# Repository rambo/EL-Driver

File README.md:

# EL driver

Trying to build as small as possible (and relatively efficiente) EL driver
for small panels/wires for wearable applications.

Currently looking at using Micrel ICs

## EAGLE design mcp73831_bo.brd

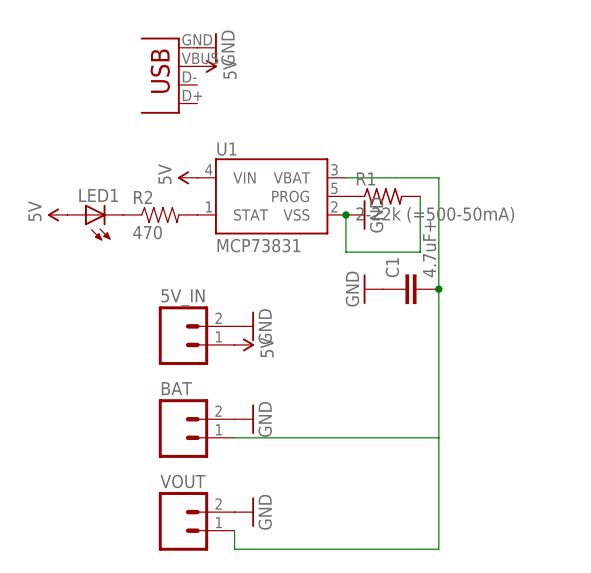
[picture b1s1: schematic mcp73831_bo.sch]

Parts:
5V_IN: M02PTH; 1X02
BAT: M02PTH; 1X02
C1: 4.7uF+; C0805
LED1: LED0603; LED-0603
R1: 2-22k (=500-50mA); M0805
R2: 470; 0603-RES
U1: MCP73831; SOT23-5
VOUT: M02PTH; 1X02
X1: USBSMD; USB-MINIB

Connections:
5V: 5V_IN.1, LED1.A, U1.4 (VIN), X1.VBUS
GND: 5V_IN.2, BAT.2, C1.1, R1.2, U1.2 (VSS), VOUT.2, X1.GND
unnamed: R2.2, U1.1 (STAT)
unnamed: LED1.C, R2.1
PROG: R1.1, U1.5 (PROG)
VBAT: BAT.1, C1.2, U1.3 (VBAT), VOUT.1

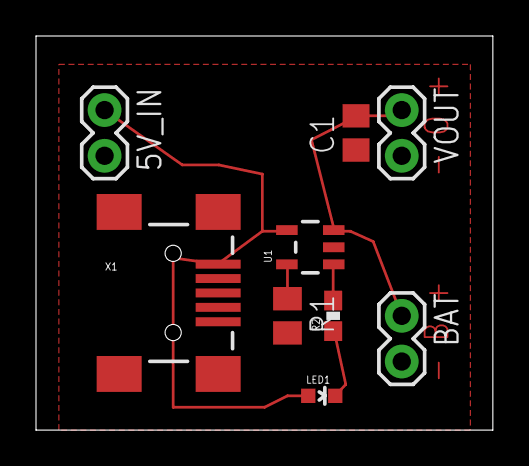
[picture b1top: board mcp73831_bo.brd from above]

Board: 1 copper layer, 25.4 x 21.9 mm, 9 parts (0 on the bottom side), 6 nets.

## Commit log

2012-01-21 IC datasheets
2012-01-21 first schematic, still missing the input cap since I need to check what I have in stock
2012-01-21 added filter cap
2012-01-21 initial placement
2012-01-21 DRC for autorouter
2012-01-21 routed protoboard
2012-01-21 smaller board, fixed broken polygon
2012-01-21 minor adjustments
2012-01-21 top layer (the only one) of the board
2012-01-21 almost same as 4830 but extra trimmer to allow higher REL (and some values adjusted)
2012-01-21 the datasheet reference has 220uH inductor for 2.7nF output cap)
2012-01-21 the top (and only) layer of the board
2012-01-21 the inductor is easy to short to ground, and the last EL trimmer is even bigger problem with copper-pour
2012-01-22 do not pour copper between inductor leads, they are easy to short to ground here
2012-01-22 the library part had pins in wrong order so I had to remake the pin connections and reroute
2012-01-22 combined etch mask
2012-01-22 this file prints incorrectly
2012-01-22 readme
2012-01-22 added a note about the ICs and library...
2012-01-22 the IC eagle symbol and package
2012-10-30 making a simple 1l breakout for this lipo-charge ic
2012-10-30 loaded my old 1layer rules
2012-10-30 gndplane
2012-10-30 routed
2012-10-30 the prog resistor sizing
2012-10-30 approve the dRC error, i aint gonna drill those holes under the usb connector
2012-10-30 there was no ready made chip for this so leaving incomplete for now

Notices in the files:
parts and their libraries:
SparkFun-PowerIC: Licensing: CC v3.0 Share-Alike You are welcome to use this library for commercial purposes.
